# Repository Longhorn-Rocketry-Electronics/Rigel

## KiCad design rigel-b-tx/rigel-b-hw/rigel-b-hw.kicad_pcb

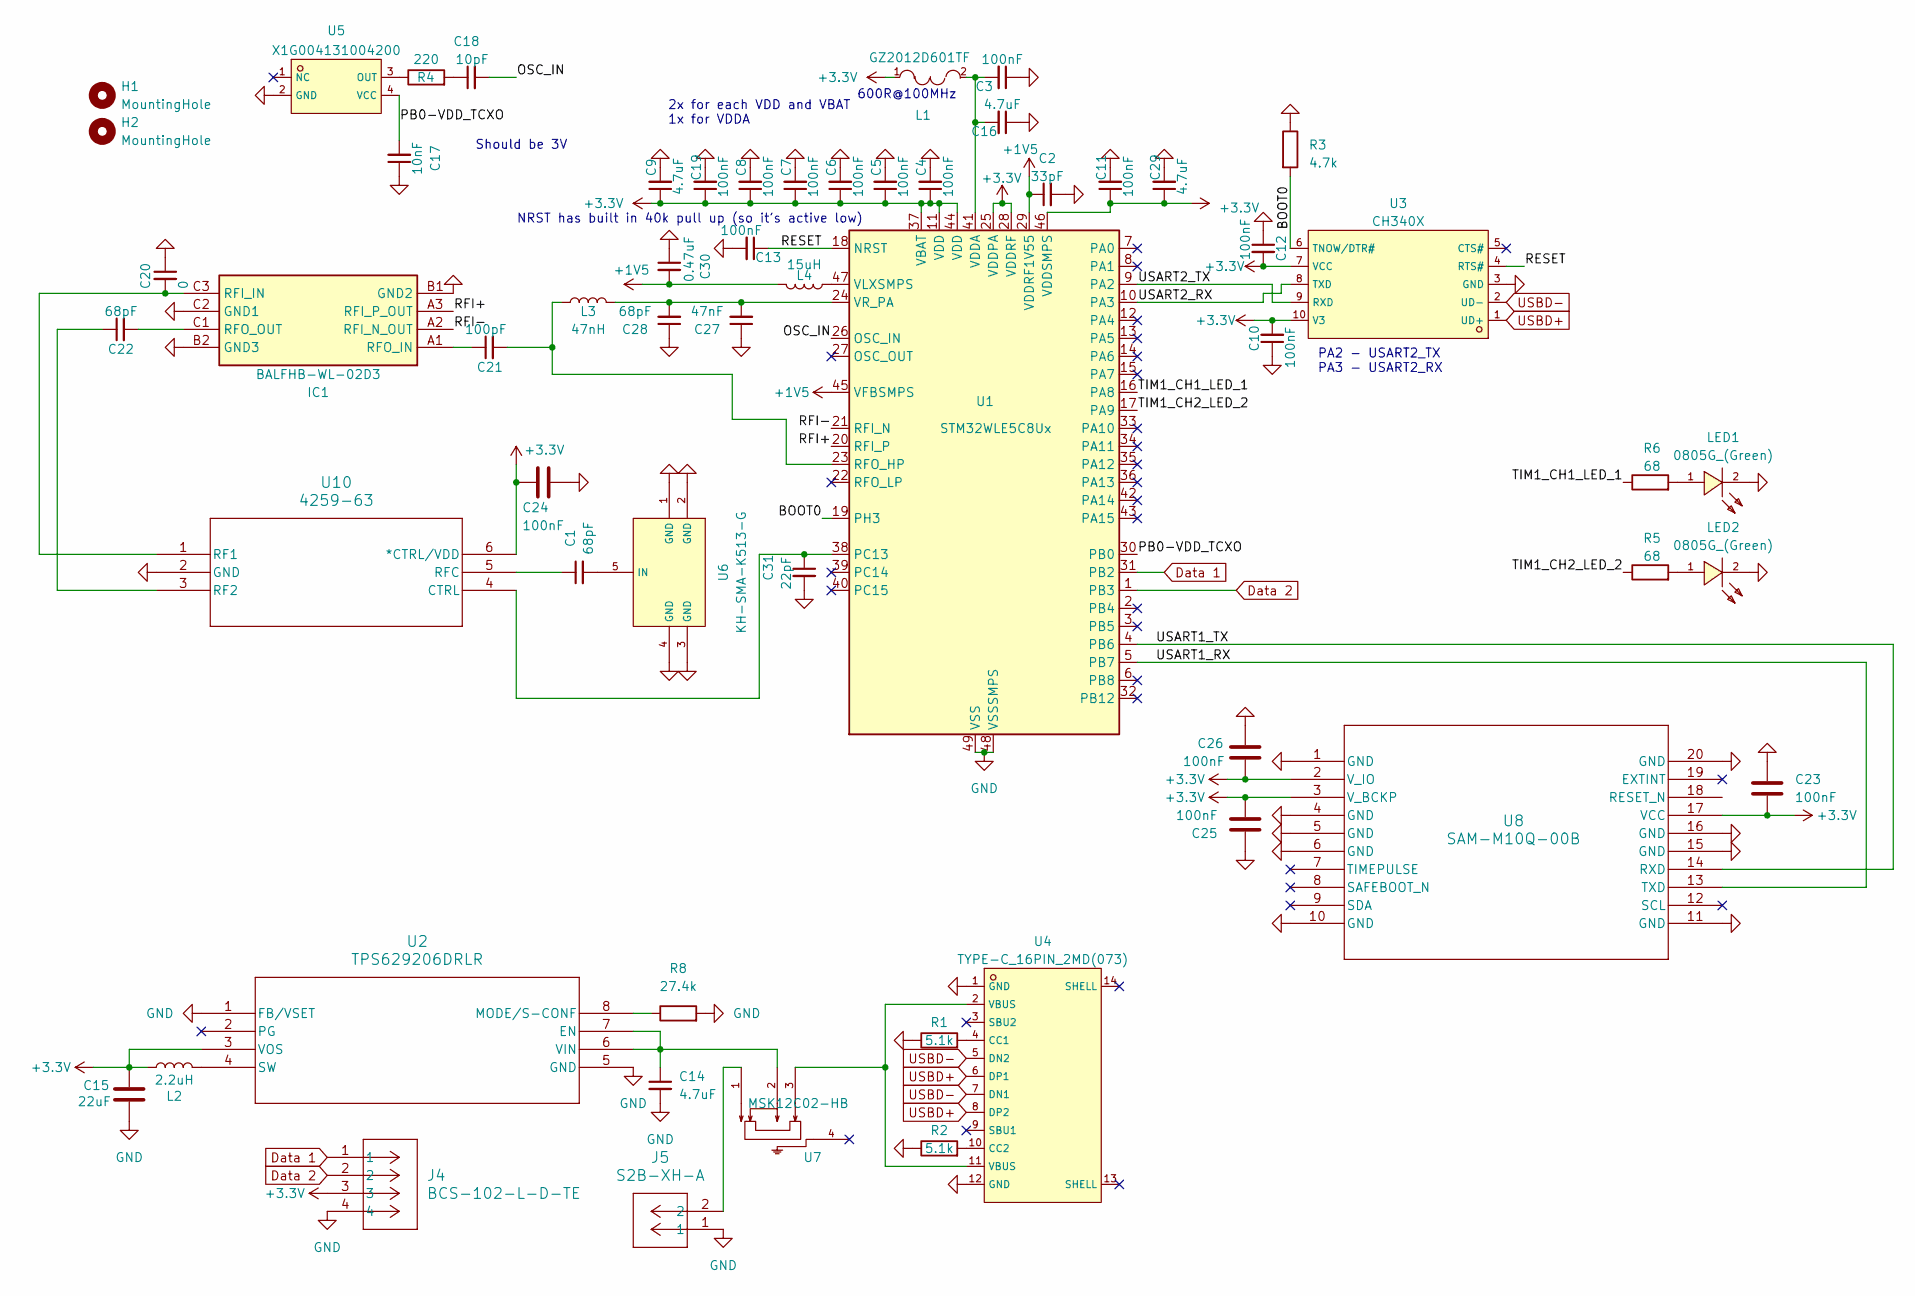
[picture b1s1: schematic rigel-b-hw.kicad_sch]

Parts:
C1, C28: 68pF; C_0603_1608Metric
C2: 33pF; C_0402_1005Metric
C3, C4, C5, C6, C7, C8, C10, C11, C12, C13, C19, C23, C24, C25, C26: 100nF; C_0402_1005Metric
C9, C14, C16: 4.7uF; C_0603_1608Metric
C15: 22uF; C_0603_1608Metric
C17: 10nF; C_0402_1005Metric
C18: 10pF; C_0402_1005Metric
C20: 0; C_0402_1005Metric; LCSC C14441
C21: 100pF; C_0402_1005Metric; LCSC C14441
C22: 68pF; C_0402_1005Metric; LCSC C14441
C27: 47nF; C_0603_1608Metric
C29: 4.7uF; C_0402_1005Metric
C30: 0.47uF; C_0603_1608Metric
C31: 22pF; C_0402_1005Metric
H1, H2: MountingHole; MountingHole_2.2mm_M2
IC1: BALFHB-WL-02D3; BALFHBWL02D3; Manufacturer_Part_Number BALFHB-WL-02D3; Mouser Part Number 511-BALFHB-WL-02D3
J4: BCS-102-L-D-TE; CON4_2X2_TU_BCS_SAI
J5: S2B-XH-A; CONN_S2B-XH-A_JST
L1: GZ2012D601TF; L0805; LCSC C1017
L2: 2.2uH; L_0603_1608Metric
L3: 47nH; L_0603_1608Metric
L4: 15uH; L_0603_1608Metric
LED1, LED2: 0805G_(Green); LED0805-R-RD; LCSC C2297
R1, R2: 5.1k; R_0402_1005Metric
R3: 4.7k; R_0402_1005Metric
R4: 220; R_0402_1005Metric
R5, R6: 68; R_0603_1608Metric
R8: 27.4k; R_0402_1005Metric
U1: STM32WLE5C8Ux; QFN-48-1EP_7x7mm_P0.5mm_EP5.6x5.6mm
U2: TPS629206DRLR; SOT5X3-8_DRL_TEX
U3: CH340X; MSOP-10_L3.0-W3.0-P0.50-LS5.0-BL; LCSC C3035748
U4: TYPE-C_16PIN_2MD(073); USB-C-SMD_TYPE-C-6PIN-2MD-073; LCSC C2765186
U5: X1G004131004200; OSC-SMD_4P-L2.0-W1.6-BL_EPSON_TG-5006CJ-19H; LCSC C7527384
U6: KH-SMA-K513-G; ANT-TH_KH-SMA-K513-G; LCSC C411575
U7: MSK12C02-HB; SW-TH_MSK12C02-HB-1; LCSC C431541
U8: SAM-M10Q-00B; SAM-M10Q_UBL
U10: 4259-63; SC-70-6_PSM

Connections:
+1V5: C2.1, C30.2, L4.2, U1.29 (VDDRF1V55), U1.45 (VFBSMPS)
+3.3V: C4.1, C5.1, C6.1, C7.1, C8.1, C9.1, C10.2, C11.1, C12.2, C15.2, C19.1, C23.2, C24.2, C25.2, C26.2, C29.1, J4.3, L1.1, L2.1, U1.11 (VDD), U1.25 (VDDPA), U1.28 (VDDRF), U1.37 (VBAT), U1.44 (VDD), U1.46 (VDDSMPS), U2.3 (VOS), U3.7 (VCC), U3.10 (V3), U8.2 (V_IO), U8.3 (V_BCKP), U8.17 (VCC), U10.6 (*CTRL/VDD)
/BOOT0: R3.2, U1.19 (PH3), U3.6 (TNOW/DTR#)
/OSC_IN: C18.2, U1.26 (OSC_IN)
/PB0-VDD_TCXO: C17.2, U1.30 (PB0), U5.4 (VCC)
/RESET: C13.1, U1.18 (NRST), U3.4 (RTS#)
/RFI+: IC1.A3 (RFI_P_OUT), U1.20 (RFI_P)
/RFI-: IC1.A2 (RFI_N_OUT), U1.21 (RFI_N)
/TIM1_CH1_LED_1: R6.1, U1.16 (PA8)
/TIM1_CH2_LED_2: R5.1, U1.17 (PA9)
/USART1_RX: U1.5 (PB7), U8.13 (TXD)
/USART1_TX: U1.4 (PB6), U8.14 (RXD)
/USART2_RX: U1.10 (PA3), U3.8 (TXD)
/USART2_TX: U1.9 (PA2), U3.9 (RXD)
Data 1: J4.1, U1.31 (PB2)
Data 2: J4.2, U1.1 (PB3)
GND: C2.2, C3.1, C4.2, C5.2, C6.2, C7.2, C8.2, C9.2, C10.1, C11.2, C12.1, C13.2, C14.2, C15.1, C16.1, C17.1, C19.2, C20.1, C23.1, C24.1, C25.1, C26.1, C27.1, C28.1, C29.2, C30.1, C31.2, IC1.B1 (GND2), IC1.B2 (GND3), IC1.C2 (GND1), J4.4, J5.1, LED1.2 (K), LED2.2 (K), R1.1, R2.1, R3.1, R8.2, U1.48 (VSSSMPS), U1.49 (VSS), U2.1 (FB/VSET), U2.5 (GND), U3.3 (GND), U4.1 (GND), U4.12 (GND), U5.2 (GND), U6.1 (GND), U6.2 (GND), U6.3 (GND), U6.4 (GND), U8.1 (GND), U8.4 (GND), U8.5 (GND), U8.6 (GND), U8.10 (GND), U8.11 (GND), U8.15 (GND), U8.16 (GND), U8.20 (GND), U10.2 (GND)
unnamed: C18.1, R4.2
unnamed: C20.2, IC1.C3 (RFI_IN), U10.1 (RF1)
unnamed: C21.1, IC1.A1 (RFO_IN)
unnamed: C22.2, IC1.C1 (RFO_OUT)
unnamed: J5.2, U7.1
unnamed: LED1.1 (A), R6.2
unnamed: LED2.1 (A), R5.2
unnamed: C31.1, U1.38 (PC13), U10.4 (CTRL)
unnamed: C21.2, L3.1, U1.23 (RFO_HP)
unnamed: C3.2, C16.2, L1.2, U1.41 (VDDA)
unnamed: L4.1, U1.47 (VLXSMPS)
unnamed: C27.2, C28.2, L3.2, U1.24 (VR_PA)
unnamed: C14.1, U2.6 (VIN), U2.7 (EN), U7.2
unnamed: R8.1, U2.8 (MODE/S-CONF)
unnamed: L2.2, U2.4 (SW)
unnamed: R1.2, U4.4 (CC1)
unnamed: R2.2, U4.10 (CC2)
unnamed: U4.2 (VBUS), U4.11 (VBUS), U7.3
unnamed: R4.1, U5.3 (OUT)
unnamed: C1.2, U6.5 (IN)
unnamed: C22.1, U10.3 (RF2)
unnamed: C1.1, U10.5 (RFC)
USBD+: U3.1 (UD+), U4.6 (DP1), U4.8 (DP2)
USBD-: U3.2 (UD-), U4.5 (DN2), U4.7 (DN1)

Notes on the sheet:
2x for each VDD and VBAT 1x for VDDA
PA2 - USART2_TX PA3 - USART2_RX
NRST has built in 40k pull up (so it's active low)
600R@100MHz
Should be 3V

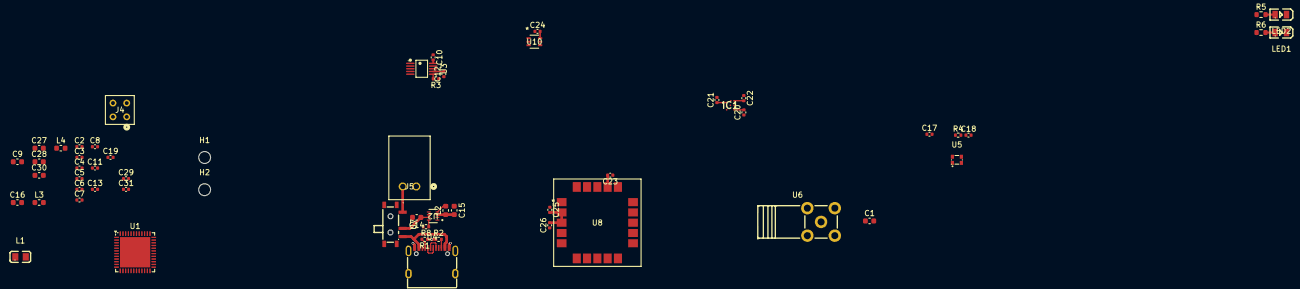
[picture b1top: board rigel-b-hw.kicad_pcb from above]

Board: 4 copper layers, 58 parts (0 on the bottom side), 41 nets.

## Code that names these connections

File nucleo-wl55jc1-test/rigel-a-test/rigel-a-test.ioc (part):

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Mcu.Name=STM32WLE5C8Ux
Mcu.Package=UFQFPN48
Mcu.UserName=STM32WLE5C8Ux
PA2.Signal=USART2_TX
PA3.Signal=USART2_RX
PA8.Signal=S_TIM1_CH1
PA9.Signal=S_TIM1_CH2
PB0-VDD_TCXO.Mode=HSE-TCXO
PB0-VDD_TCXO.Signal=VDDTCXO
RCC.HSE_VALUE=32000000
board=custom

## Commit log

2024-01-11 begin rigel a schematic
2024-01-17 schematic mostly done except pi filter
2024-02-24 begin sw and finish schematic (pre kicad 8)
2024-02-24 migrate to v8
2024-02-26 Pretty much finish layout
2024-02-26 add finishing touches to pcb
2024-04-11 basic RX test working
2024-10-20 create rigel b tx kicad project
2024-10-22 Copy rigel a to rigel b
2024-10-27 Added new footprint
2024-10-27 Added part of new buck converter
2024-10-27 Update resistor value
2024-10-29 Finish buck converter
2024-11-03 Buck converter + power switch
2024-11-03 Battery connector
2024-11-05 gnss symbol + footprint schematic
2024-11-05 Diodes
2024-11-05 Revert "Diodes"
    This reverts commit 9fc2fa8655eb56a1ed53d9832a2dacb5bb0fa527.
2024-11-05 Revert "gnss symbol + footprint schematic"
    This reverts commit cef04a5809bb9187b891c4147c2a1f02ae79041f.
2024-11-05 gnss footprint + symbol schematic
2024-11-10 gnss schematic+footprint
2024-11-10 added gnd to GPS
2024-11-10 added rigel tx test code
2024-11-10 RF Switch
2024-11-10 Connection
2024-11-12 Board to Board & Battery Connectors
2024-11-12 Update connections based off example schematic
    https://www.st.com/resource/en/schematic_pack/mb1848-hp-schematic.pdf
2024-11-17 Footprints. Done with Schematic
2024-11-19 PCB Layout ALMOST done
2024-12-03 PCB Layout
2025-02-07 RF Switch finalized
2025-02-07 Added a capacitor for the switch
2025-02-21 New Switch
2025-02-28 connected PB2 and PB3 to Data 1 and Data 2 (for data transfer from Polaris)
2025-03-01 Added Datasheets
2025-03-01 Began some traces
    Waiting on Polaris. Started tracing individual systems.
